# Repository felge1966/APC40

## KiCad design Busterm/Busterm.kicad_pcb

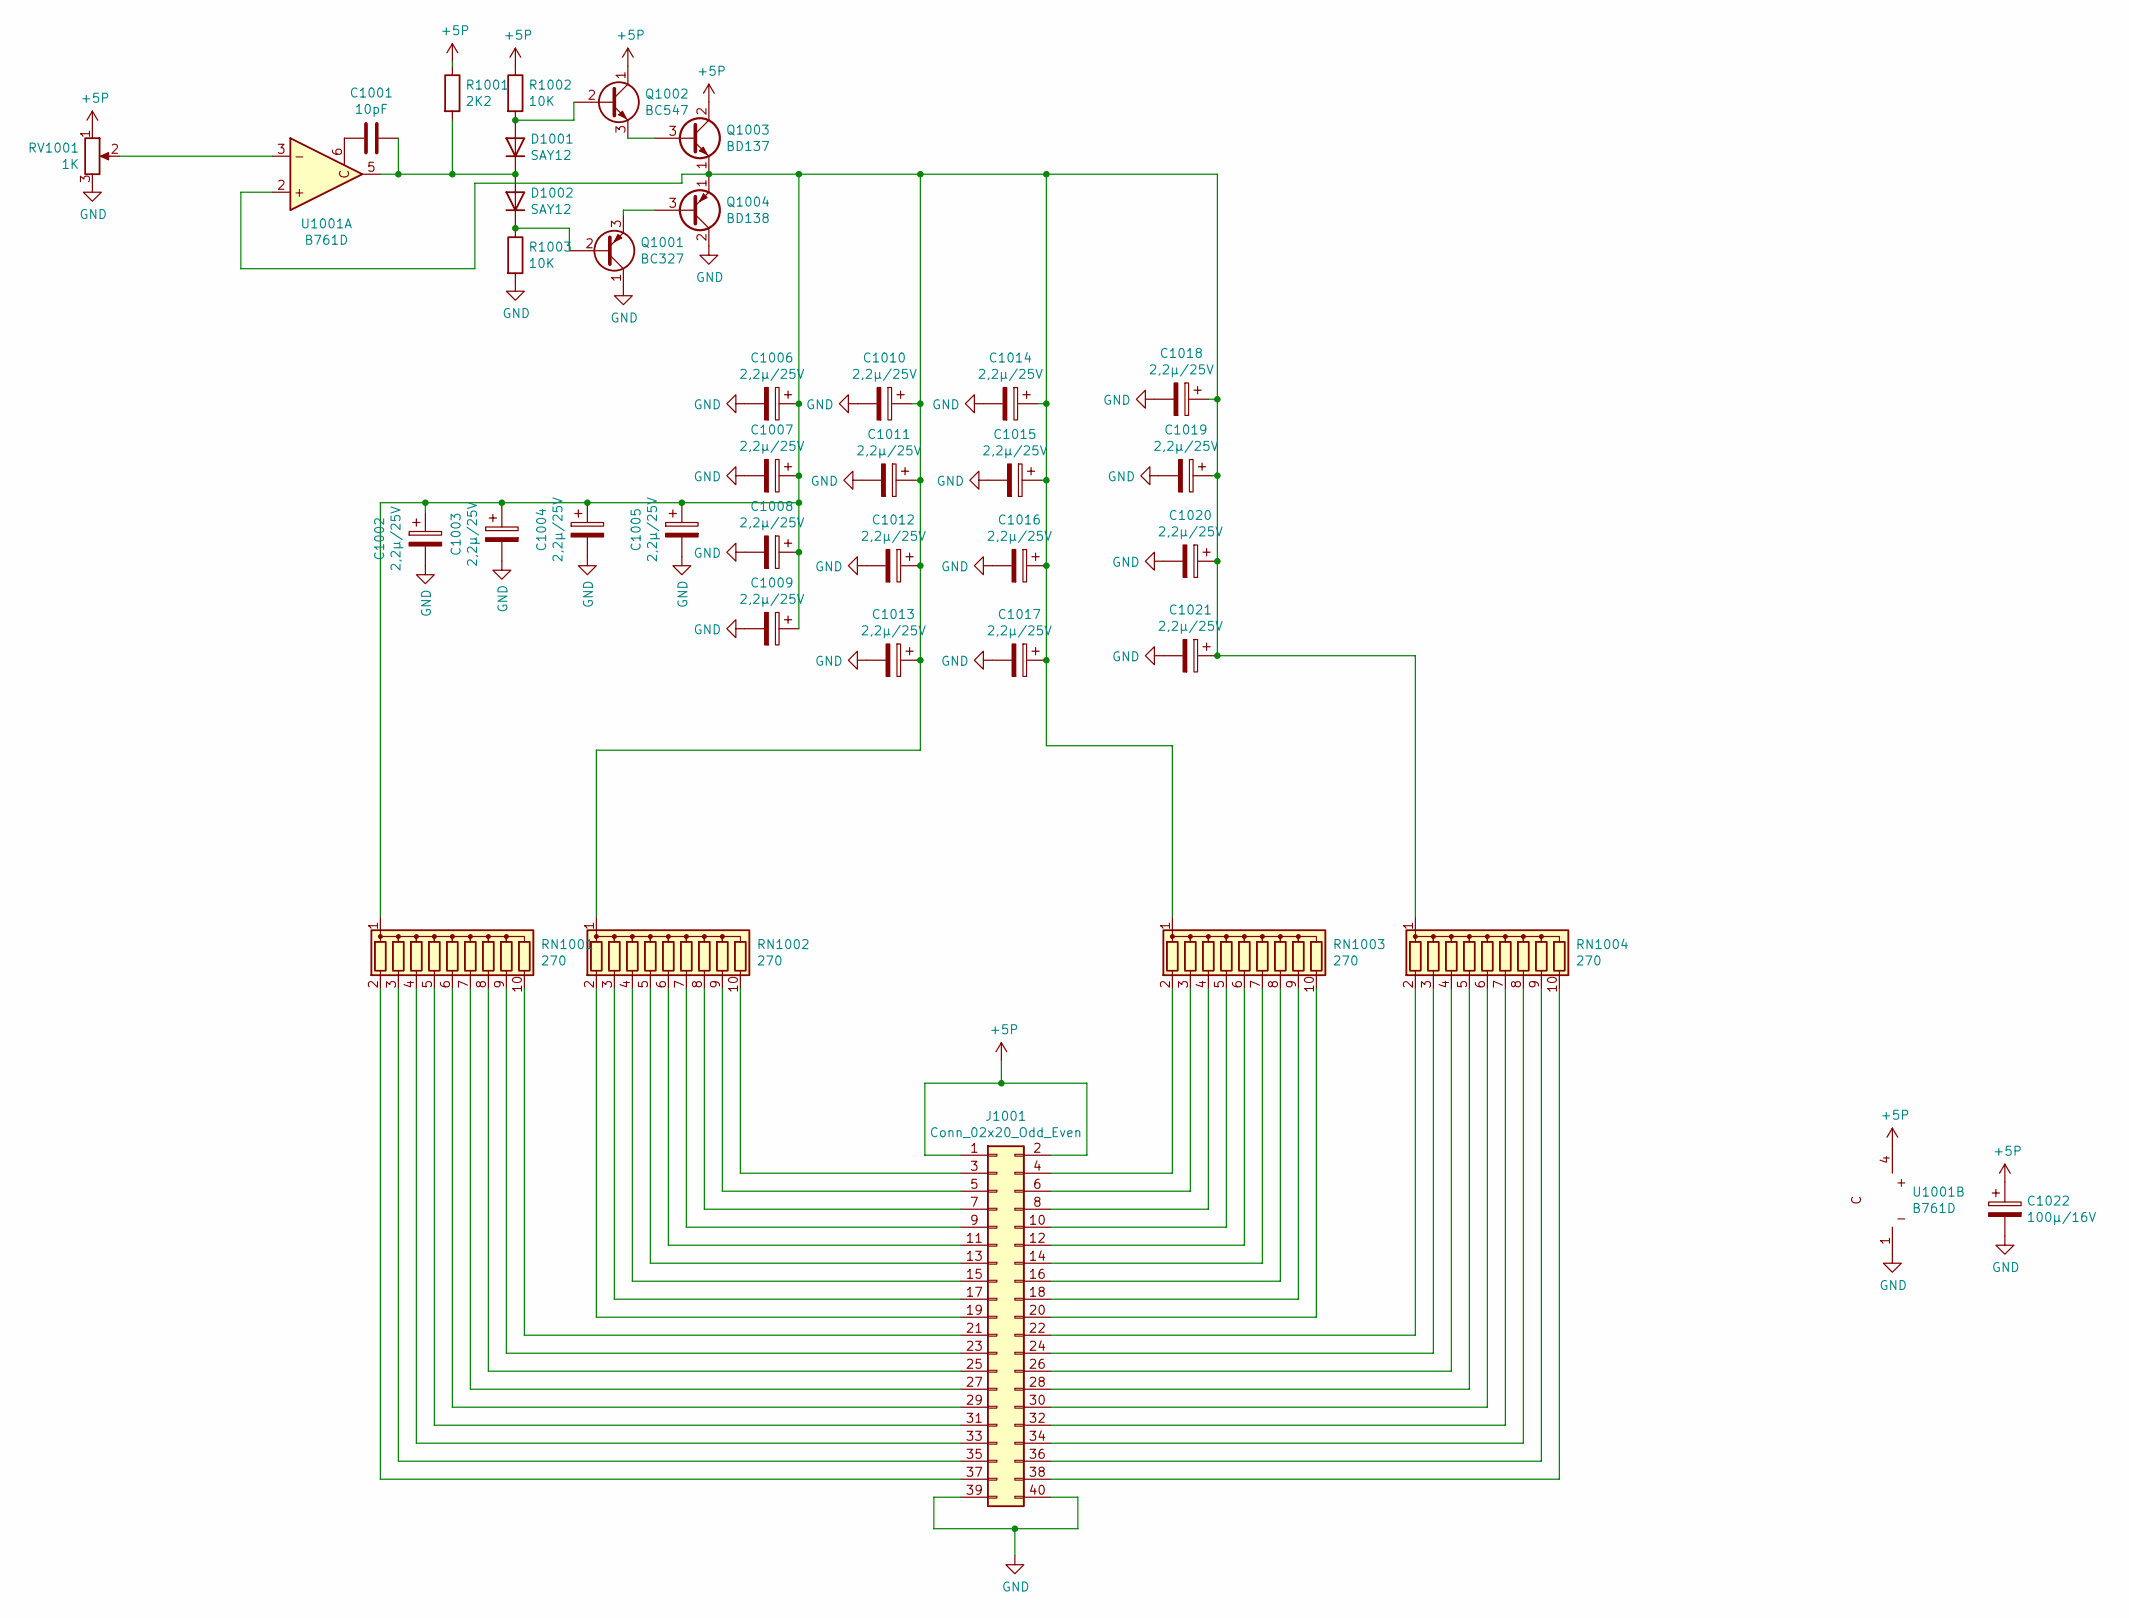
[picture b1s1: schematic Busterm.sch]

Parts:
C1001: 10pF; C_Disc_D3.0mm_W2.0mm_P2.50mm
C1002, C1003, C1004, C1005, C1006, C1007, C1008, C1009, C1010, C1011, C1012, C1013, C1014, C1015, C1016, C1017, C1018, C1019, C1020, C1021: 2,2µ/25V; CP_Radial_D4.0mm_P2.00mm
C1022: 100µ/16V; CP_Radial_D5.0mm_P2.50mm
D1001, D1002: SAY12; D_DO-15_P2.54mm_Vertical_AnodeUp
J1001: Conn_02x20_Odd_Even; PinHeader_2x20_P2.54mm_Vertical
Q1001: BC327; TO-92_Inline
Q1002: BC547; TO-92_Inline
Q1003: BD137; TO-126-3_Vertical
Q1004: BD138; TO-126-3_Vertical
R1001: 2K2; R_Axial_DIN0207_L6.3mm_D2.5mm_P10.16mm_Horizontal
R1002, R1003: 10K; R_Axial_DIN0207_L6.3mm_D2.5mm_P10.16mm_Horizontal
RN1001, RN1002, RN1003, RN1004: 270; R_Array_SIP10
RV1001: 1K; Potentiometer_Piher_PT-10-H01_Horizontal
U1001: B761D; DIP-6_W7.62mm

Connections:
+5P: C1022.1, J1001.1, J1001.2, Q1002.1 (C), Q1003.2 (C), R1001.1, R1002.1, RV1001.1, U1001.4 (-)
GND: C1002.2, C1003.2, C1004.2, C1005.2, C1006.2, C1007.2, C1008.2, C1009.2, C1010.2, C1011.2, C1012.2, C1013.2, C1014.2, C1015.2, C1016.2, C1017.2, C1018.2, C1019.2, C1020.2, C1021.2, C1022.2, J1001.39, J1001.40, Q1001.1 (C), Q1004.2 (C), R1003.2, RV1001.3, U1001.1 (+)
unnamed: C1001.1, D1001.1 (K), D1002.2 (A), R1001.2, U1001.5
unnamed: C1001.2, U1001.6 (C)
unnamed: C1002.1, C1003.1, C1004.1, C1005.1, C1006.1, C1007.1, C1008.1, C1009.1, C1010.1, C1011.1, C1012.1, C1013.1, C1014.1, C1015.1, C1016.1, C1017.1, C1018.1, C1019.1, C1020.1, C1021.1, Q1003.1 (E), Q1004.1 (E), RN1001.1 (common), RN1002.1 (common), RN1003.1 (common), RN1004.1 (common), U1001.2 (+)
unnamed: D1001.2 (A), Q1002.2 (B), R1002.2
unnamed: D1002.1 (K), Q1001.2 (B), R1003.1
unnamed: J1001.3, RN1002.10 (R9)
unnamed: J1001.4, RN1003.2 (R1)
unnamed: J1001.5, RN1002.9 (R8)
unnamed: J1001.6, RN1003.3 (R2)
unnamed: J1001.7, RN1002.8 (R7)
unnamed: J1001.8, RN1003.4 (R3)
unnamed: J1001.9, RN1002.7 (R6)
unnamed: J1001.10, RN1003.5 (R4)
unnamed: J1001.11, RN1002.6 (R5)
unnamed: J1001.12, RN1003.6 (R5)
unnamed: J1001.13, RN1002.5 (R4)
unnamed: J1001.14, RN1003.7 (R6)
unnamed: J1001.15, RN1002.4 (R3)
unnamed: J1001.16, RN1003.8 (R7)
unnamed: J1001.17, RN1002.3 (R2)
unnamed: J1001.18, RN1003.9 (R8)
unnamed: J1001.19, RN1002.2 (R1)
unnamed: J1001.20, RN1003.10 (R9)
unnamed: J1001.21, RN1001.10 (R9)
unnamed: J1001.22, RN1004.2 (R1)
unnamed: J1001.23, RN1001.9 (R8)
unnamed: J1001.24, RN1004.3 (R2)
unnamed: J1001.25, RN1001.8 (R7)
unnamed: J1001.26, RN1004.4 (R3)
unnamed: J1001.27, RN1001.7 (R6)
unnamed: J1001.28, RN1004.5 (R4)
unnamed: J1001.29, RN1001.6 (R5)
unnamed: J1001.30, RN1004.6 (R5)
unnamed: J1001.31, RN1001.5 (R4)
unnamed: J1001.32, RN1004.7 (R6)
unnamed: J1001.33, RN1001.4 (R3)
unnamed: J1001.34, RN1004.8 (R7)
unnamed: J1001.35, RN1001.3 (R2)
unnamed: J1001.36, RN1004.9 (R8)
unnamed: J1001.37, RN1001.2 (R1)
unnamed: J1001.38, RN1004.10 (R9)
unnamed: Q1001.3 (E), Q1004.3 (B)
unnamed: Q1002.3 (E), Q1003.3 (B)
unnamed: RV1001.2, U1001.3 (-)

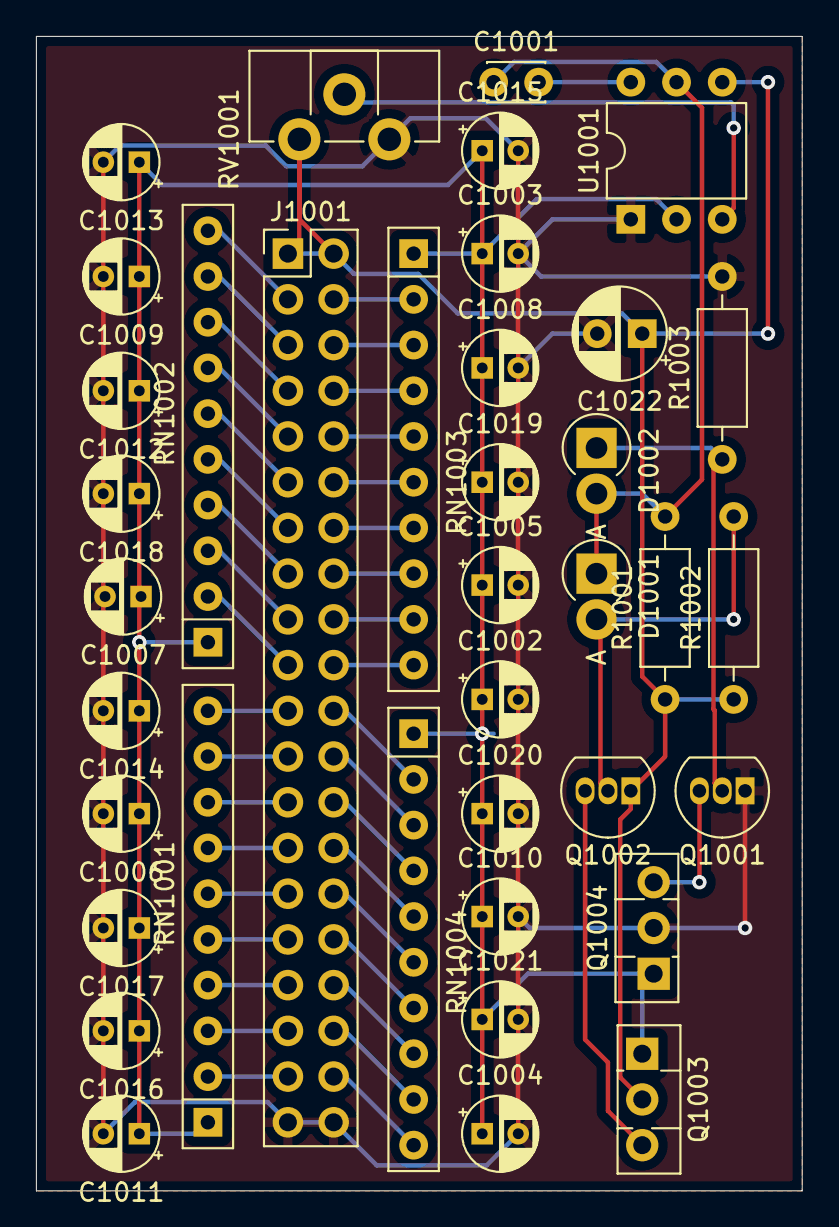
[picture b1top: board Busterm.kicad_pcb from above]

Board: 2 copper layers, 42.5 x 64.1 mm, 38 parts (0 on the bottom side), 46 nets.

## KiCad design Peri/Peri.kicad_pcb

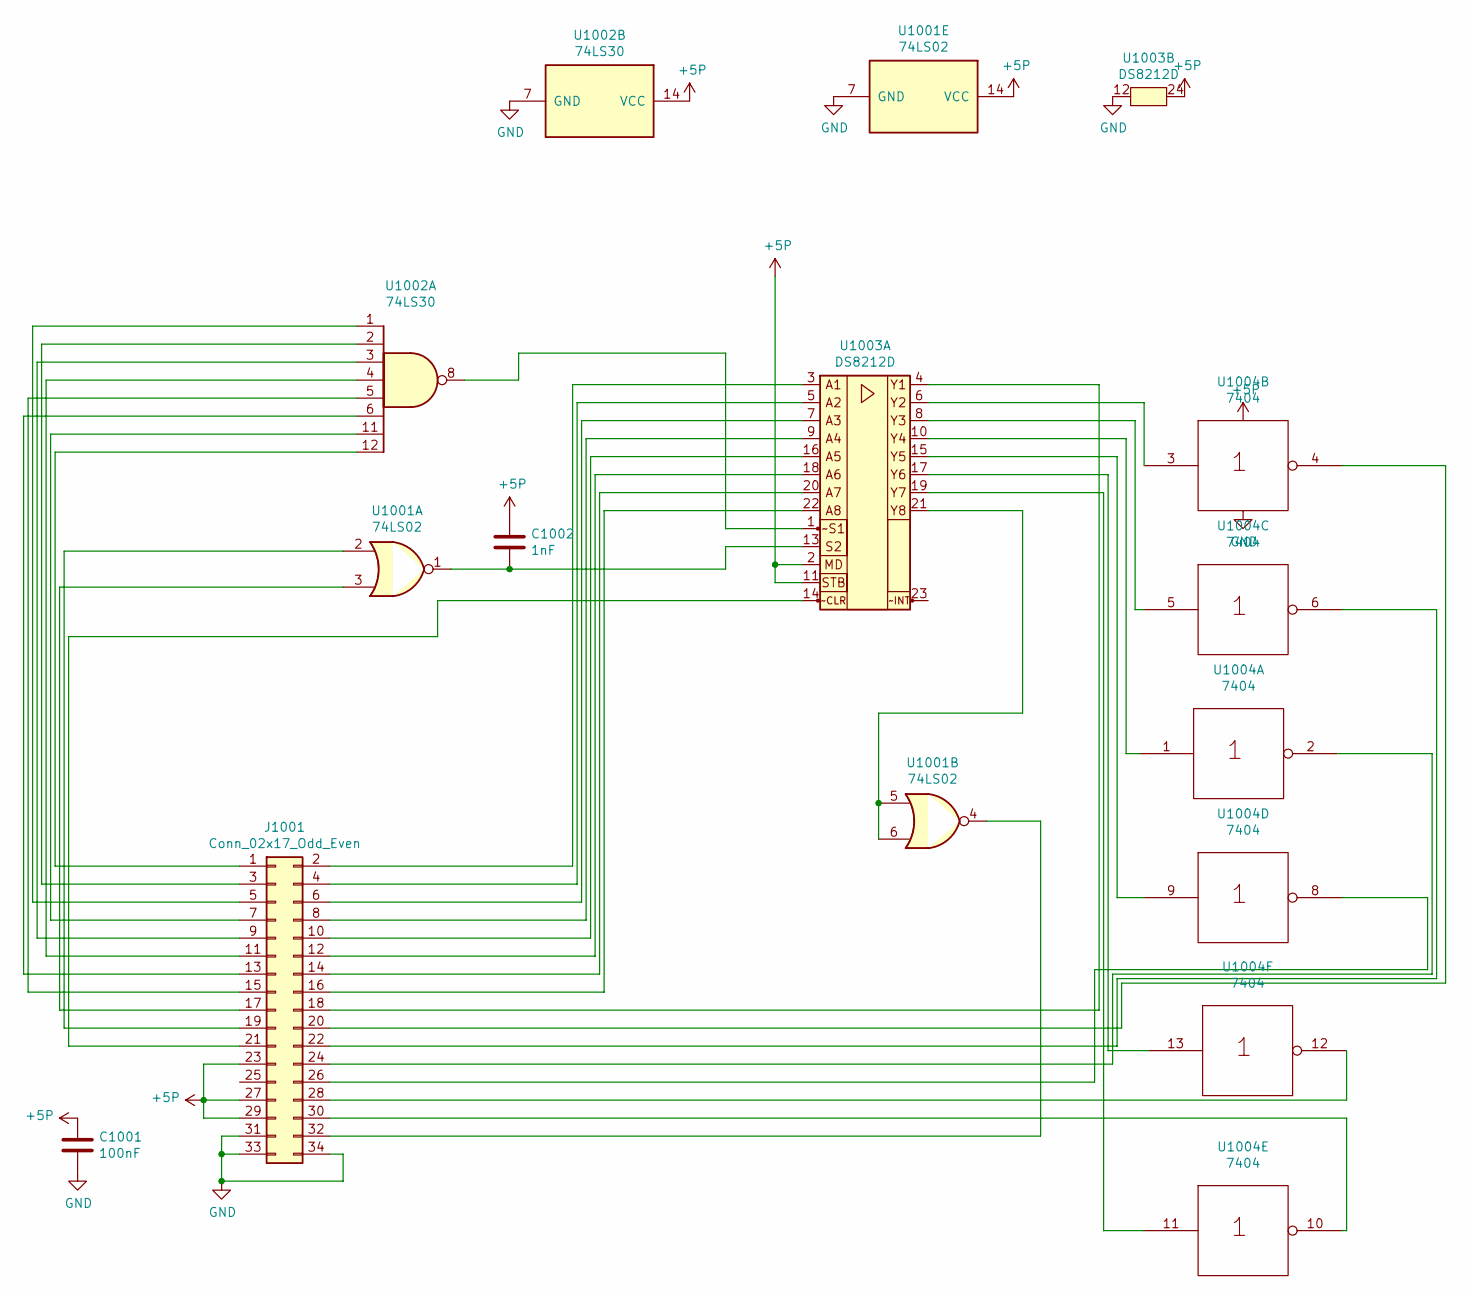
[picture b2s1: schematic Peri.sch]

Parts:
C1001: 100nF; C_Disc_D3.0mm_W1.6mm_P2.50mm
C1002: 1nF; C_Disc_D3.0mm_W1.6mm_P2.50mm
J1001: Conn_02x17_Odd_Even; PinSocket_2x17_P2.54mm_Vertical
U1001: 74LS02; DIP-14_W7.62mm_LongPads
U1002: 74LS30; DIP-14_W7.62mm_LongPads
U1003: DS8212D; DIP-24_W15.24mm_LongPads
U1004: 7404; DIP-14_W7.62mm_LongPads

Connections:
+5P: C1001.1, C1002.2, J1001.23, J1001.27, J1001.29, U1001.14 (VCC), U1002.14 (VCC), U1003.2 (MD), U1003.11 (STB), U1003.24 (Vcc), U1004.14 (Vcc)
GND: C1001.2, J1001.31, J1001.33, J1001.34, U1001.7 (GND), U1002.7 (GND), U1003.12 (GND), U1004.7 (Gnd)
unnamed: C1002.1, U1001.1, U1003.13 (S2)
unnamed: J1001.1, U1002.12
unnamed: J1001.2, U1003.3 (A1)
unnamed: J1001.3, U1002.2
unnamed: J1001.4, U1003.5 (A2)
unnamed: J1001.5, U1002.1
unnamed: J1001.6, U1003.7 (A3)
unnamed: J1001.7, U1002.11
unnamed: J1001.8, U1003.9 (A4)
unnamed: J1001.9, U1002.3
unnamed: J1001.10, U1003.16 (A5)
unnamed: J1001.11, U1002.4
unnamed: J1001.12, U1003.18 (A6)
unnamed: J1001.13, U1002.6
unnamed: J1001.14, U1003.20 (A7)
unnamed: J1001.15, U1002.5
unnamed: J1001.16, U1003.22 (A8)
unnamed: J1001.17, U1001.3
unnamed: J1001.18, U1003.4 (Y1)
unnamed: J1001.19, U1001.2
unnamed: J1001.20, U1004.4
unnamed: J1001.21, U1003.14 (~CLR)
unnamed: J1001.22, U1004.6
unnamed: J1001.24, U1004.2
unnamed: J1001.26, U1004.8
unnamed: J1001.28, U1004.12
unnamed: J1001.30, U1004.10
unnamed: J1001.32, U1001.4
unnamed: U1001.5, U1001.6, U1003.21 (Y8)
unnamed: U1002.8, U1003.1 (~S1)
unnamed: U1003.6 (Y2), U1004.3
unnamed: U1003.8 (Y3), U1004.5
unnamed: U1003.10 (A4), U1004.1
unnamed: U1003.15 (Y5), U1004.9
unnamed: U1003.17 (Y6), U1004.13
unnamed: U1003.19 (Y7), U1004.11

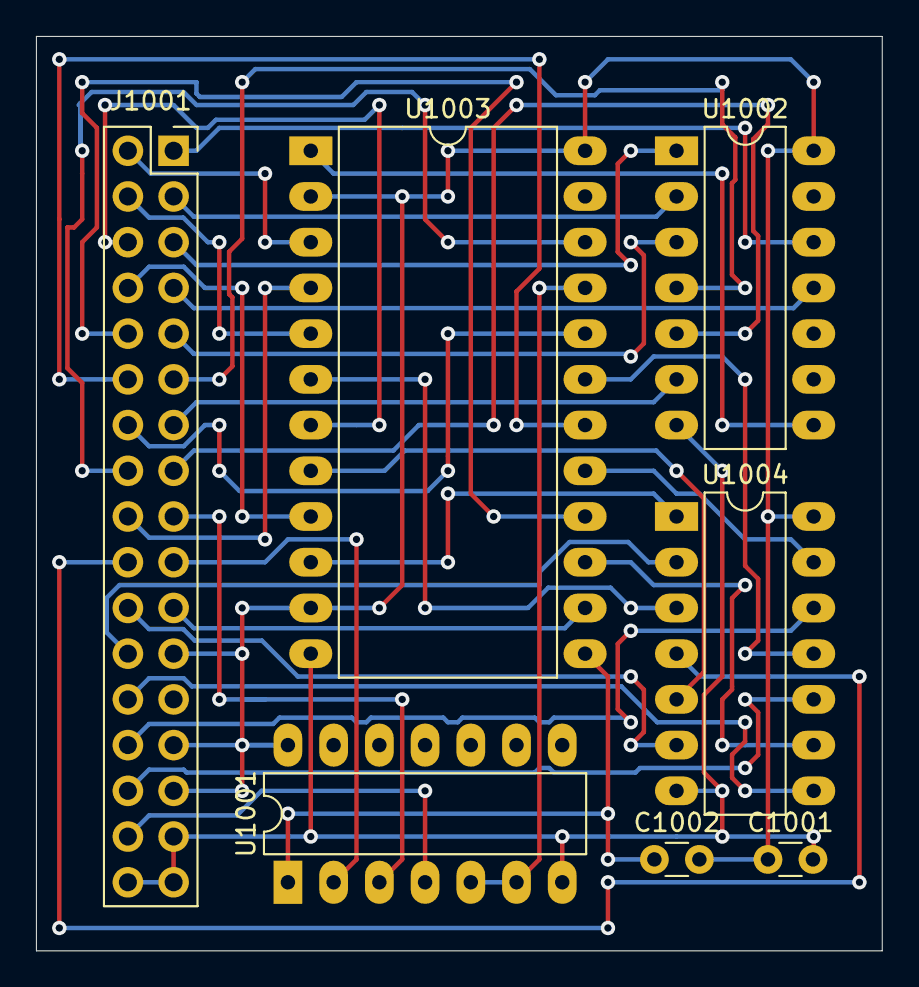
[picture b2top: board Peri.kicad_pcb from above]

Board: 2 copper layers, 47.0 x 50.8 mm, 7 parts (0 on the bottom side), 38 nets.
